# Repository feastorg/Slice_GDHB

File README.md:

# Gate-Driven H-Bridge Slice

Gate-driven Discrete H-Bridge Slice for BREAD.

## Introduction

[Short introduction on the project.]

## Usage

[Explain how to use the project. Include examples and screenshots if applicable.]

## Ratings

| Item | Rating |
| --- | --- |
| Motor current | 10 A continuous |
| VBB (motor supply, J2.3 to J2.1) | 24 V max |
| Logic | 5 V from the slice bus (Nano and A4957 VDD) |

- **Fuse the motor supply.** An inline 15 A fuse in the VBB lead, outside
  the board, is required. The board has no fuse, no current limit or
  current sense, and no reverse-polarity protection; D2 (SMCJ26A) clamps
  VBB transients only (about 35 V at 10 A, under the FETs' 40 V).
- **Use synchronous rectification.** At 10 A a body diode carrying the
  freewheel current dissipates about 4 W. Drive leg A at 20 kHz with
  complementary AHI/ALO (Timer1 OC1A/OC1B) and hold leg B static for
  direction.
- **Ramp the duty cycle (soft start).** The bridge has 440 uF of bulk
  capacitance and no inrush or current limiting.
- **Order 1 oz copper on all four layers** (1.6 mm); the copper is sized
  for 10 A at a 20 C rise on 1 oz.
- PGND (FET sources, bulk caps, J2.1) joins the logic GND only at NT2,
  beside U2.

No firmware ships with this board yet.

## Nano pin map

| A4957 input | Net | Nano pin |
| --- | --- | --- |
| AHI (leg A high side) | AHI1 | D9 (Timer1 OC1A) |
| ALO (leg A low side) | ALO1 | D10 (Timer1 OC1B) |
| BHI (leg B high side) | BHI1 | D11 |
| BLO (leg B low side) | BLO1 | D6 |
| FAULT (open drain, low = fault) | FAULT1 | A0 |
| RESET (low = sleep) | RESET1 | A1 |

AHI and BHI swapped pins in November 2026 (AHI was on D11, BHI on D9), so
Timer1's two outputs drive both switches of leg A.

## Bill of materials

`documentation/BOM_GDHB_v0.ods` and `documentation/BREAD_Slice.csv` predate
this revision (they list the old parts and counts) and are stale. Take the
BOM from the schematic (KiCad: Tools > Generate BOM, or
`kicad-cli sch export bom`); the MPN field carries the part numbers.

## Design notes

- **C9 (VREG) is 10 uF, not 20 x CBOOT after DC bias.** The A4957
  datasheet (A4957-DS Rev. 2, "VREG Capacitor Selection", p. 10) sizes
  the VREG capacitor to limit the VREG drop when a low-side turn-on and
  a bootstrap recharge come together, and calls 20 x CBOOT "a
  reasonable value". With CBOOT = 330 nF (C7, C8) that is 6.6 uF.
  C9 (Murata GRM31CR71E106KA12L, 10 uF 25 V X7R 1206) keeps about 3.5 uF at 13 V on KEMET's
  DC-bias curve for the comparable C1206C106K3RACTU (-65%), about
  2.9 uF at VREG max (13.9 V) and -10% tolerance: 9 to 11 x CBOOT
  (313 nF at 13 V).
  The drop it has to hold is one low-side gate charge plus one
  bootstrap recharge, 2 x 98 nC (CSD18512Q5B Qg max at 10 V): 56 mV
  at 3.5 uF, 68 mV at 2.9 uF. VREG is 12.65 V minimum and its
  undervoltage lockout trips at 5.85 V maximum (VREGUVOFF, p. 5), so
  the margin is over 6.7 V. Charging both bootstrap capacitors from
  0 V at once out of C9 alone (2 x 330 nF x 12 V) would pull VREG
  down 2.7 V, still about 4 V above the lockout. The regulator's
  average load at 20 kHz with one leg switching (2 x 98 nC x 20 kHz,
  3.9 mA) is inside the 8 mA its 12.65 V minimum is specified at
  (p. 4).
- **NT2 (the only GND-PGND join) sits beside U2, not at the bulk
  capacitor's negative.** The A4957 layout notes (p. 11, first bullet,
  and Figure 2) return GND and the MOSFET sources separately to the
  negative of the motor-supply filter capacitor. Here that would tie
  GND at C5.2 or C6.2, 25-35 mm away through the VBB/PGND planes, and
  carry the low-side gate returns through it: the GLA/GLB gate loops
  would grow from about 24/28 mm2 to 177/529 mm2 (C5.2) or 997/537 mm2
  (C6.2). Beside U2, NT2 lands on the PGND pour that holds cell A's
  ceramic negatives (C16.2 is 6.2 mm away), which keeps those loops
  small. The datasheet calls its layout notes "only recommendations"
  and asks for each design to be tested at maximum current (p. 11):
  check the GND-PGND difference and low-side VGS ringing at 10 A.

## Documentation

Please refer to the [docs](/docs) for more info.

---

<div align="center">
  
</div>

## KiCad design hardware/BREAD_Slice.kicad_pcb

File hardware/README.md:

# Hardware Notes

- Driver A4957SESTR-T
  - https://www.digikey.ca/en/products/detail/allegro-microsystems/A4957SESTR-T/3770630
- wago terminal block:
  - https://www.digikey.ca/en/products/detail/wago-corporation/2606-1104-010-000/15538173
- MOSFETs: TI CSD18512Q5B (40 V, 1.6 mOhm max at 10 V, SON 5x6 on the LFPAK56 land)
  - https://www.ti.com/lit/ds/symlink/csd18512q5b.pdf
-

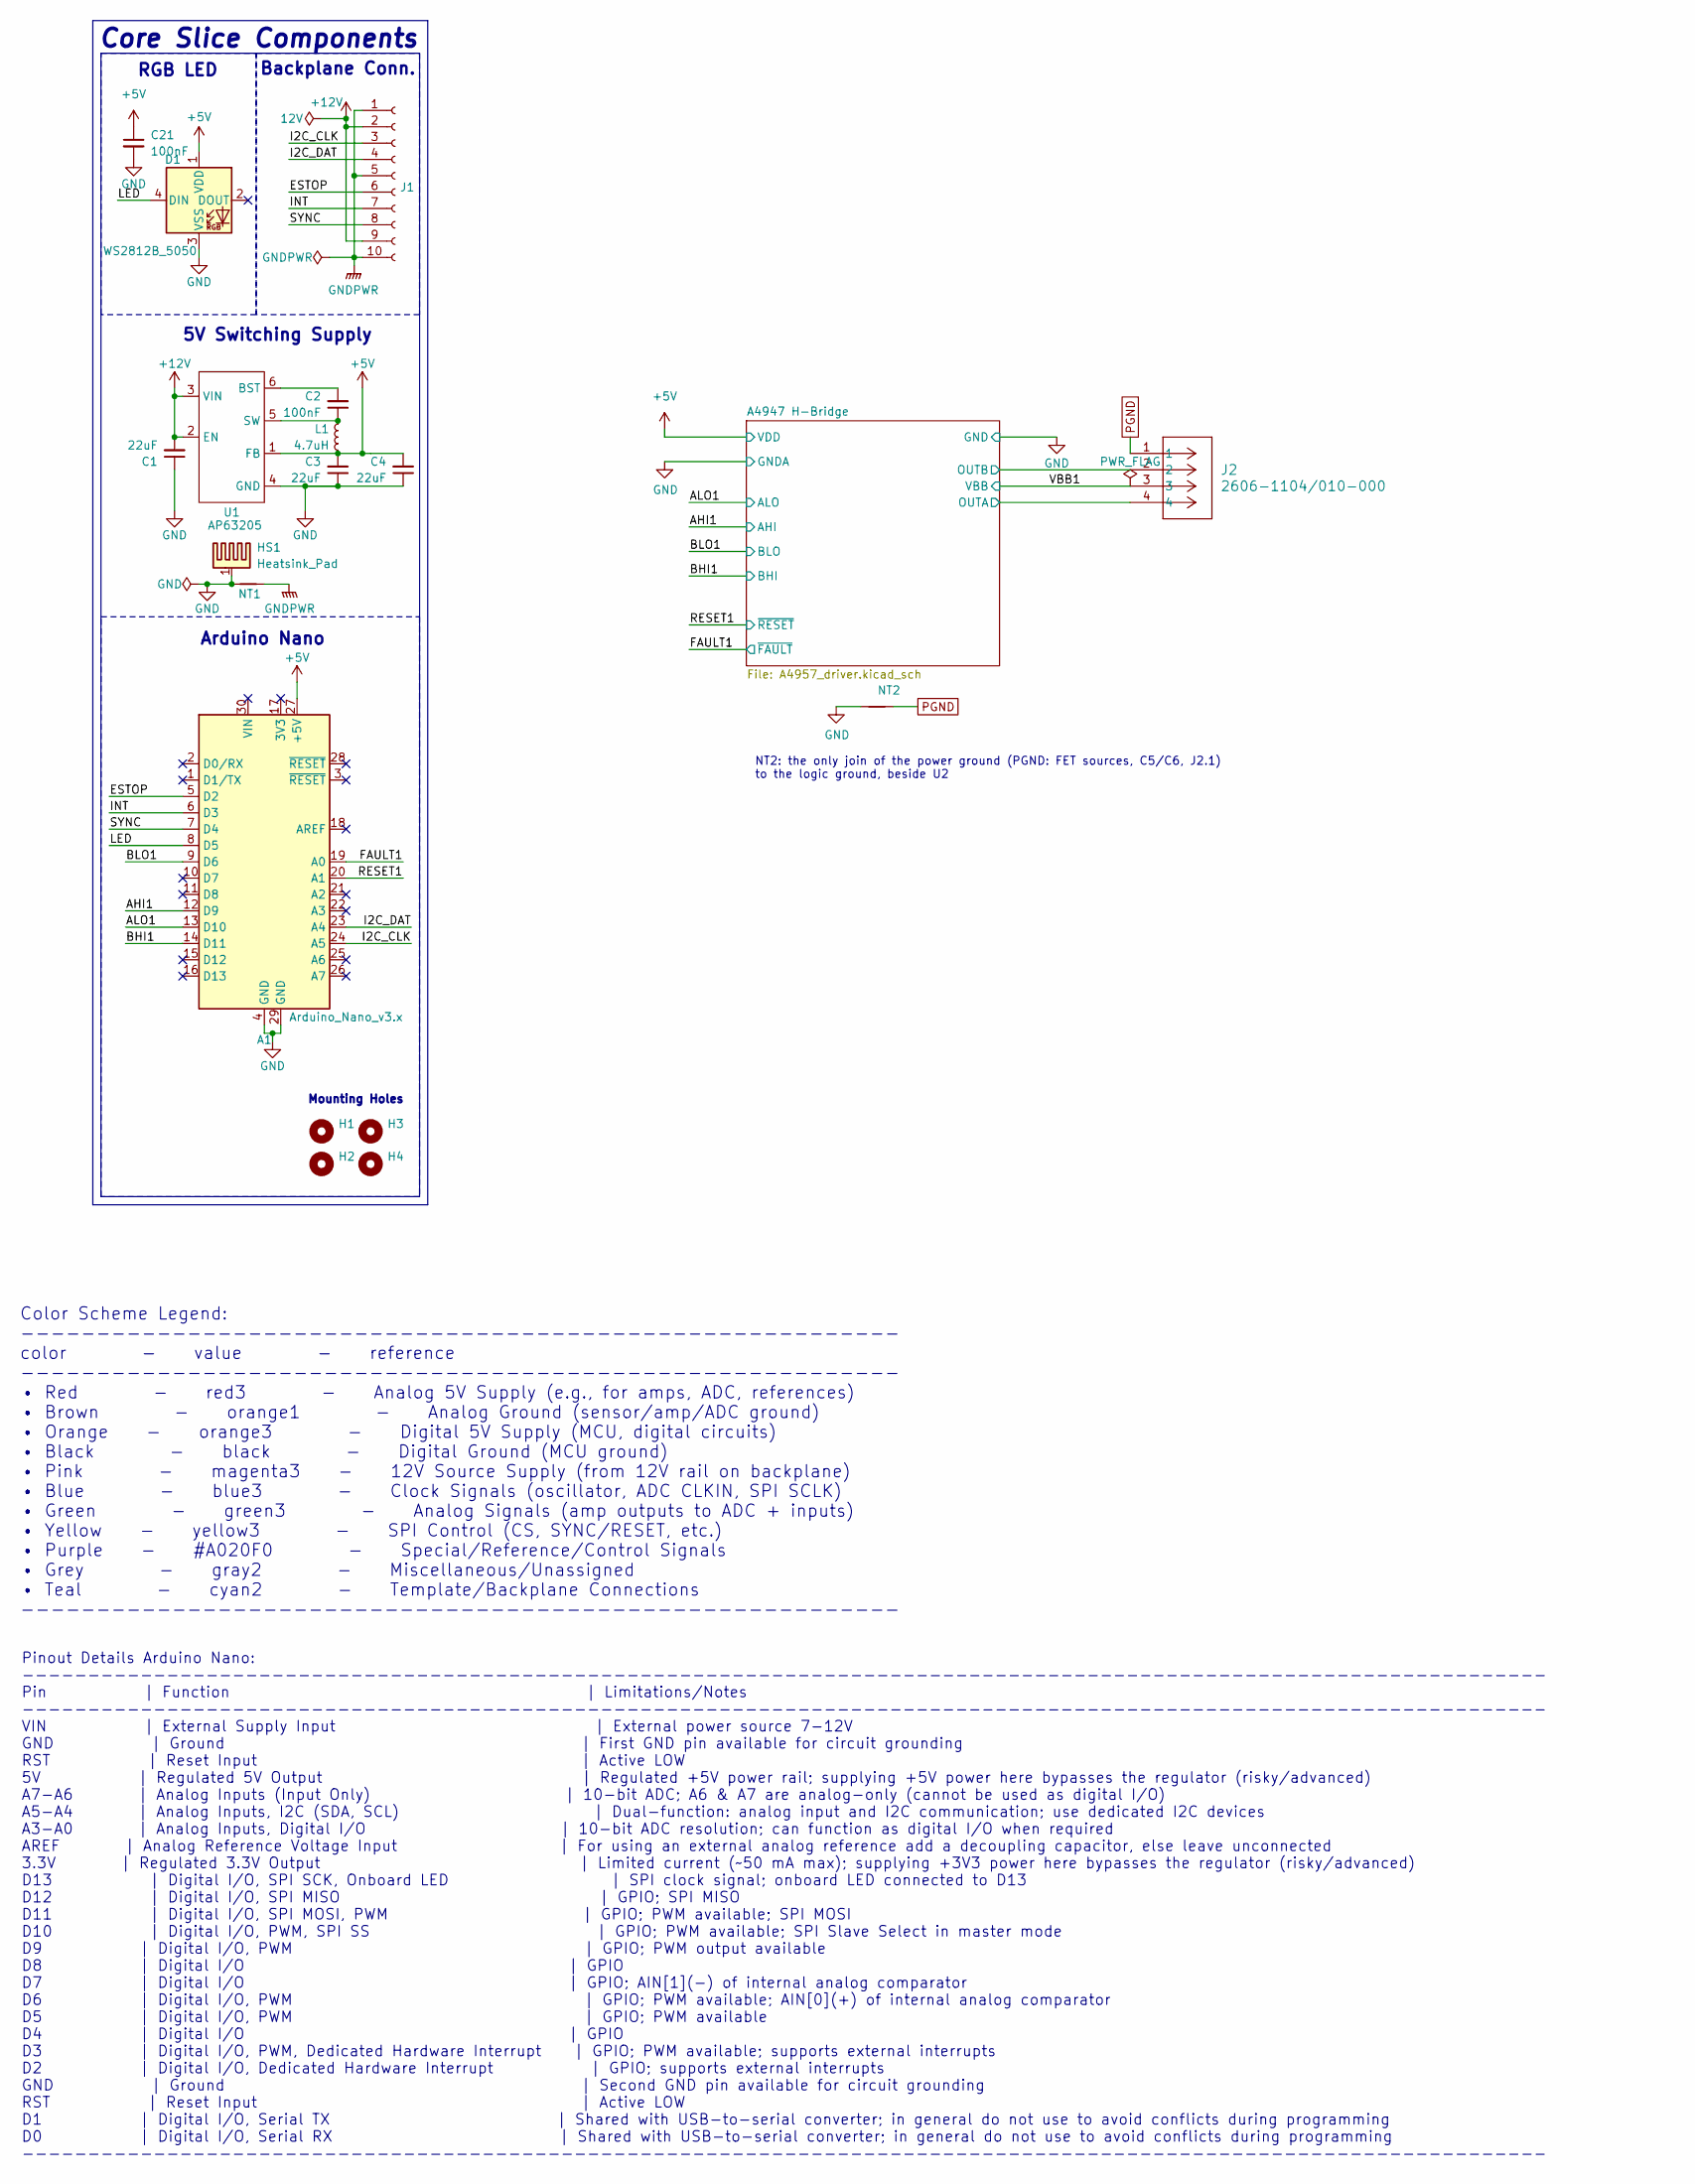
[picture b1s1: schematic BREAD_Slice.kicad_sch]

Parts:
A1: Arduino_Nano_v3.x; Arduino_Nano
C1, C3, C4: 22uF; C_1206_3216Metric_Pad1.33x1.80mm_HandSolder
C2: 100nF; C_1206_3216Metric_Pad1.33x1.80mm_HandSolder
C21: 100nF; C_0805_2012Metric_Pad1.18x1.45mm_HandSolder; MPN GRM21BR71H104KA01L
D1: WS2812B_5050; WS2812-5050-4PIN
H1, H2, H3, H4: MountingHole; MountingHole_5mm
HS1: Heatsink_Pad; Thermal_Pad
J1: Conn_01x10_Female; PinSocket_1x10_P2.54mm_Horizontal
J2: 2606-1104/010-000; 2606-1104_010-000_WAGO
L1: 4.7uH; L_1210_3225Metric
NT1, NT2: NetTie_2; NetTie-2_SMD_Pad2.0mm
U1: AP63205; TSOT-23-6

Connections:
+5V: A1.27 (+5V), C3.2, C4.2, C21.1, D1.1 (VDD), L1.2, U1.1 (FB); also elsewhere on the board
+12V: C1.2, J1.2, J1.9, U1.2 (EN), U1.3 (VIN)
/A4947 H-Bridge/SA: J2.4; also elsewhere on the board
/A4947 H-Bridge/SB: J2.2; also elsewhere on the board
/AHI1: A1.12 (D9); also elsewhere on the board
/ALO1: A1.13 (D10); also elsewhere on the board
/BHI1: A1.14 (D11); also elsewhere on the board
/BLO1: A1.9 (D6); also elsewhere on the board
/ESTOP: A1.5 (D2), J1.6
/FAULT1: A1.19 (A0); also elsewhere on the board
/I2C_CLK: A1.24 (A5), J1.3
/I2C_DAT: A1.23 (A4), J1.4
/INT: A1.6 (D3), J1.7
/LED: A1.8 (D5), D1.4 (DIN)
/RESET1: A1.20 (A1); also elsewhere on the board
/SYNC: A1.7 (D4), J1.8
/VBB1: J2.3; also elsewhere on the board
GND: A1.4 (GND), A1.29 (GND), C1.1, C3.1, C4.1, C21.2, D1.3 (VSS), HS1.1, NT1.1, NT2.1, U1.4 (GND); also elsewhere on the board
GNDPWR: J1.1, J1.5, J1.10, NT1.2
unnamed: C2.2, U1.6 (BST)
unnamed: C2.1, L1.1, U1.5 (SW)
PGND: J2.1, NT2.2; also elsewhere on the board

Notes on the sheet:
5V Switching Supply
Pinout Details Arduino Nano: -------------------------------------------------------------------------------------------------------------------- Pin | Function | Limitations/Notes -------------------------------------------------------------------------------------------------------------------- V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
RGB LED
Color Scheme Legend: ---------------------------------------------------------- color - value - reference ---------------------------------------------------------- • Red - red3 - Analog 5V Supply (e.g., for amps, ADC, references) • Brown - orange1 - Analog Ground (sensor/amp/ADC ground) • Orange -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
Core Slice Components
Arduino Nano
Mounting Holes
Backplane Conn.
NT2: the only join of the power ground (PGND: FET sources, C5/C6, J2.1) to the logic ground, beside U2

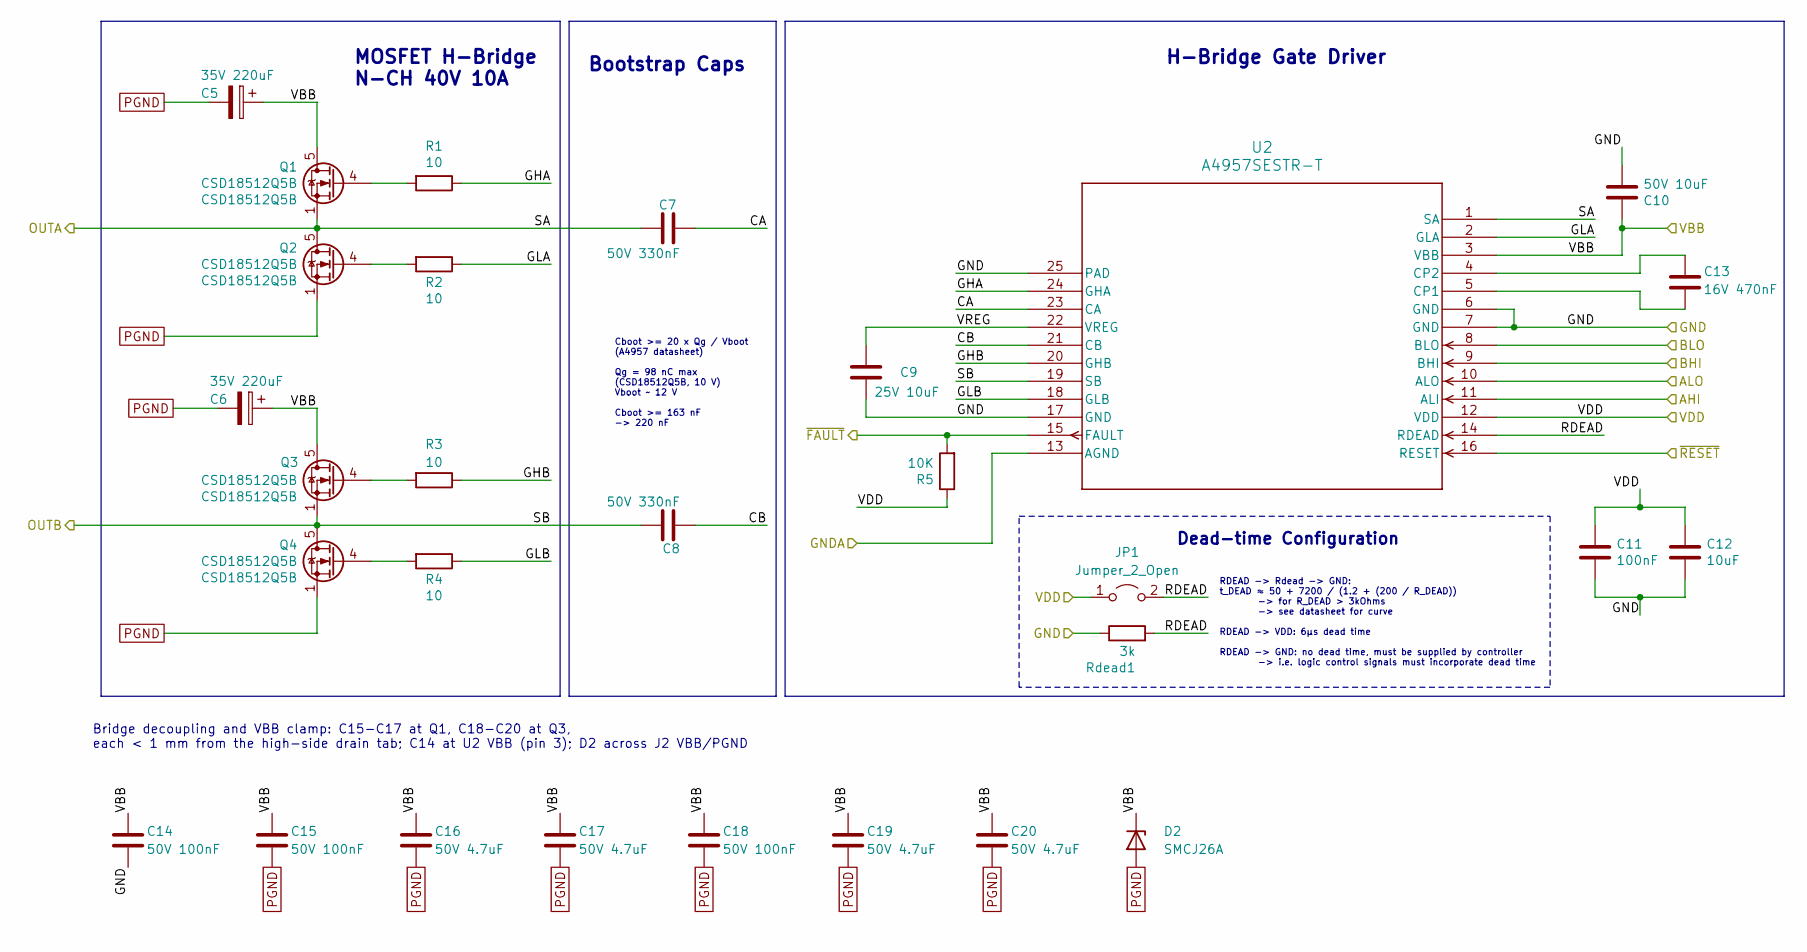
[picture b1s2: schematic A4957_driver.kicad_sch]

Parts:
C5, C6: 35V 220uF; CP_Elec_10x10; MPN EEH-ZA1V221P
C7, C8: 50V 330nF; C_0805_2012Metric_Pad1.18x1.45mm_HandSolder; MPN C0805C334K5RACTU
C9: 25V 10uF; C_1206_3216Metric; MPN GRM31CR71E106KA12L
C10: 50V 10uF; C_0805_2012Metric_Pad1.18x1.45mm_HandSolder
C11: 100nF; C_0805_2012Metric_Pad1.18x1.45mm_HandSolder
C12: 10uF; C_0805_2012Metric_Pad1.18x1.45mm_HandSolder
C13: 16V 470nF; C_0805_2012Metric_Pad1.18x1.45mm_HandSolder
C14, C15, C18: 50V 100nF; C_0603_1608Metric; MPN GRM188R71H104KA93D
C16, C17, C19, C20: 50V 4.7uF; C_1206_3216Metric; MPN GRM31CR71H475KA12L
D2: SMCJ26A; D_SMC; MPN SMCJ26A
JP1: Jumper_2_Open; C_0805_2012Metric
Q1, Q2, Q3, Q4: CSD18512Q5B; LFPAK56; MPN CSD18512Q5B
R1, R2, R3, R4: 10; R_0603_1608Metric; MPN CRCW060310R0FKEA
R5: 10K; R_0805_2012Metric_Pad1.20x1.40mm_HandSolder
Rdead1: 3k; R_0805_2012Metric_Pad1.20x1.40mm_HandSolder
U2: A4957SESTR-T; QFN-24_ALM

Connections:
+5V: C11.1, C12.1, JP1.1 (A), R5.1, U2.12 (VDD); also elsewhere on the board
/A4947 H-Bridge/CA: C7.2, U2.23 (CA)
/A4947 H-Bridge/CB: C8.2, U2.21 (CB)
/A4947 H-Bridge/GHA: R1.1, U2.24 (GHA)
/A4947 H-Bridge/GHB: R3.1, U2.20 (GHB)
/A4947 H-Bridge/GLA: R2.1, U2.2 (GLA)
/A4947 H-Bridge/GLB: R4.1, U2.18 (GLB)
/A4947 H-Bridge/RDEAD: JP1.2 (B), Rdead1.2, U2.14 (RDEAD)
/A4947 H-Bridge/SA: C7.1, Q1.1 (S), Q1.2 (S), Q1.3 (S), Q2.5 (D), U2.1 (SA); also elsewhere on the board
/A4947 H-Bridge/SB: C8.1, Q3.1 (S), Q3.2 (S), Q3.3 (S), Q4.5 (D), U2.19 (SB); also elsewhere on the board
/A4947 H-Bridge/VREG: C9.1, U2.22 (VREG)
/AHI1: U2.11 (ALI); also elsewhere on the board
/ALO1: U2.10 (ALO); also elsewhere on the board
/BHI1: U2.9 (BHI); also elsewhere on the board
/BLO1: U2.8 (BLO); also elsewhere on the board
/FAULT1: R5.2, U2.15 (FAULT); also elsewhere on the board
/RESET1: U2.16 (RESET); also elsewhere on the board
/VBB1: C5.1, C6.1, C10.1, C14.1, C15.1, C16.1, C17.1, C18.1, C19.1, C20.1, D2.1 (K), Q1.5 (D), Q3.5 (D), U2.3 (VBB); also elsewhere on the board
GND: C9.2, C10.2, C11.2, C12.2, C14.2, Rdead1.1, U2.6 (GND), U2.7 (GND), U2.13 (AGND), U2.17 (GND), U2.25 (PAD); also elsewhere on the board
unnamed: Q1.4 (G), R1.2
unnamed: Q2.4 (G), R2.2
unnamed: Q3.4 (G), R3.2
unnamed: Q4.4 (G), R4.2
unnamed: C13.1, U2.5 (CP1)
unnamed: C13.2, U2.4 (CP2)
PGND: C5.2, C6.2, C15.2, C16.2, C17.2, C18.2, C19.2, C20.2, D2.2 (A), Q2.1 (S), Q2.2 (S), Q2.3 (S), Q4.1 (S), Q4.2 (S), Q4.3 (S); also elsewhere on the board

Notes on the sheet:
Dead-time Configuration
Cboot >= 20 x Qg / Vboot (A4957 datasheet) Qg = 98 nC max (CSD18512Q5B, 10 V) Vboot ~ 12 V Cboot >= 163 nF -> 220 nF
Bootstrap Caps
RDEAD -> Rdead -> GND: t_DEAD ≈ 50 + 7200 / (1.2 + (200 / R_DEAD)) -> for R_DEAD > 3kOhms -> see datasheet for curve RDEAD -> VDD: 6µs dead time RDEAD -> GND: no dead time, must be supplied by controller -> i.e. logic control signals must incorporate dead time
H-Bridge Gate Driver
MOSFET H-Bridge N-CH 40V 10A
Bridge decoupling and VBB clamp: C15-C17 at Q1, C18-C20 at Q3, each < 1 mm from the high-side drain tab; C14 at U2 VBB (pin 3); D2 across J2 VBB/PGND

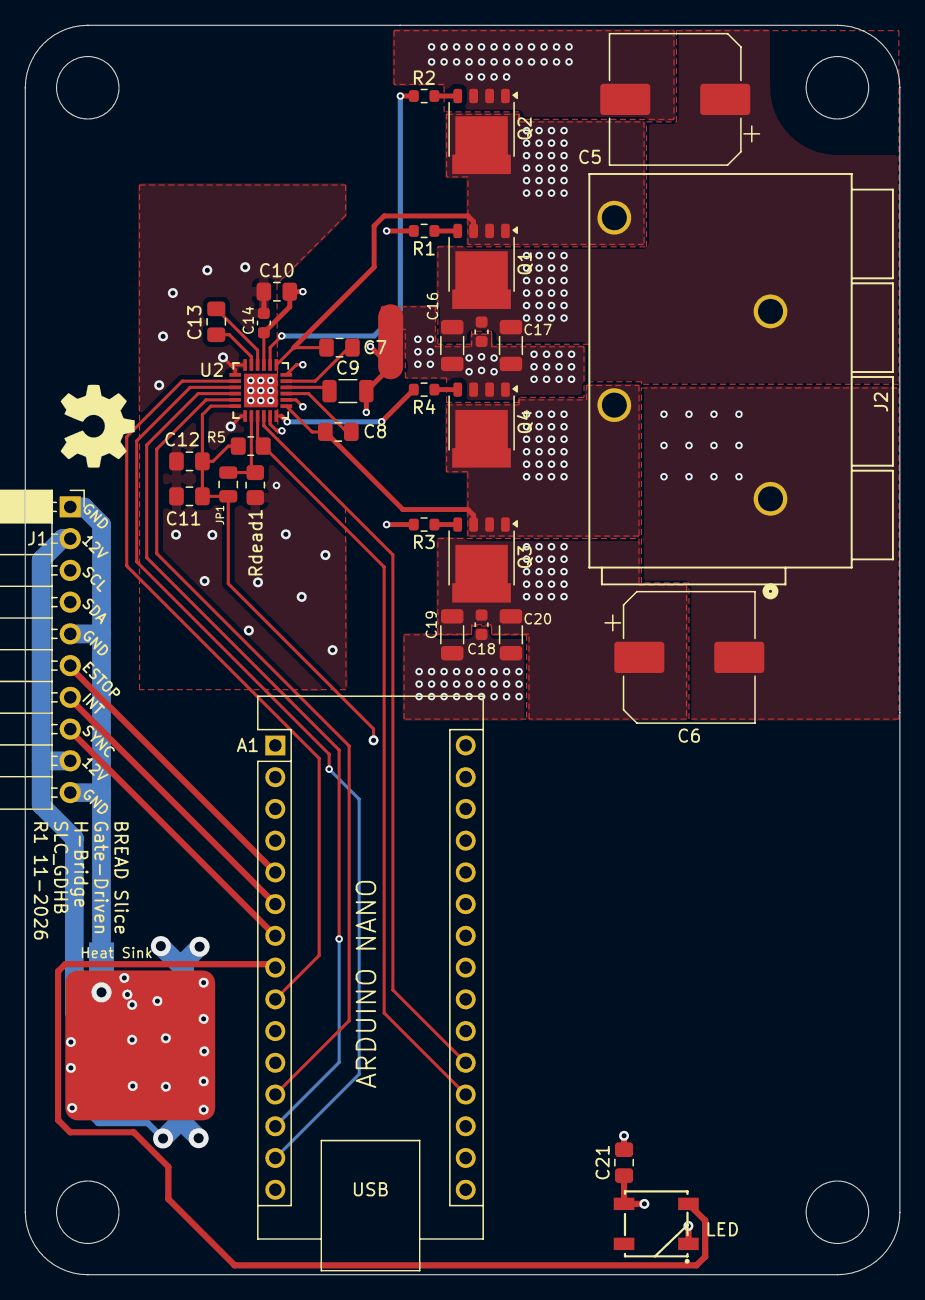
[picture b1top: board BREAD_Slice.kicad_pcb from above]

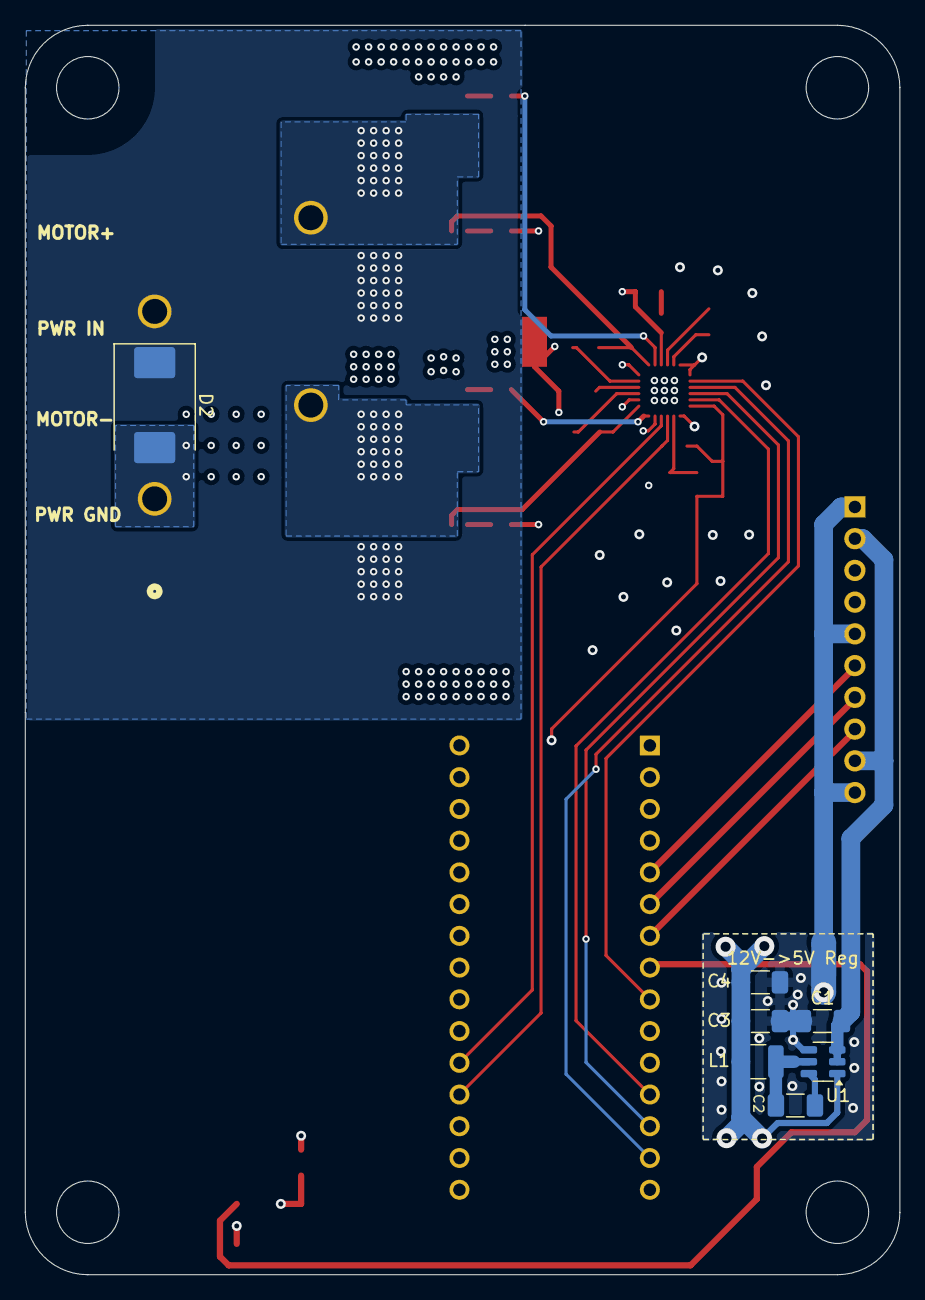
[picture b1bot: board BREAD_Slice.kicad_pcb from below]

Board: 4 copper layers, 70.0 x 100.0 mm, 48 parts (8 on the bottom side), 36 nets.

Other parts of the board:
Logo1: Logo_Open_Hardware_Small; OSHW-Symbol_6.7x6mm_SilkScreen

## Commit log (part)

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2024-07-10 initial layout poisitions done
2024-09-10 set repo
2025-04-10 finished initial schematic and board
2025-04-10 removed old
2025-04-10 added hw readme
2025-04-10 updated hw readme
2026-04-18 chore: generate gerbers
2026-05-20 Add slice.yaml manifest (schema v1.0)
2026-05-24 Add KiBot/docs pipeline (4-layer)
2026-05-24 Update TODO with CI findings (DRC+ERC errors)
